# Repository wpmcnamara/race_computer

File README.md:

# Open Road Race Timing Computer

## Version 1.0

A repository with the code for the Open Road Race Timing Computer created by Patrick McNamara.

Includes the computer's software, as well as hardware description files for both the case and PCB.

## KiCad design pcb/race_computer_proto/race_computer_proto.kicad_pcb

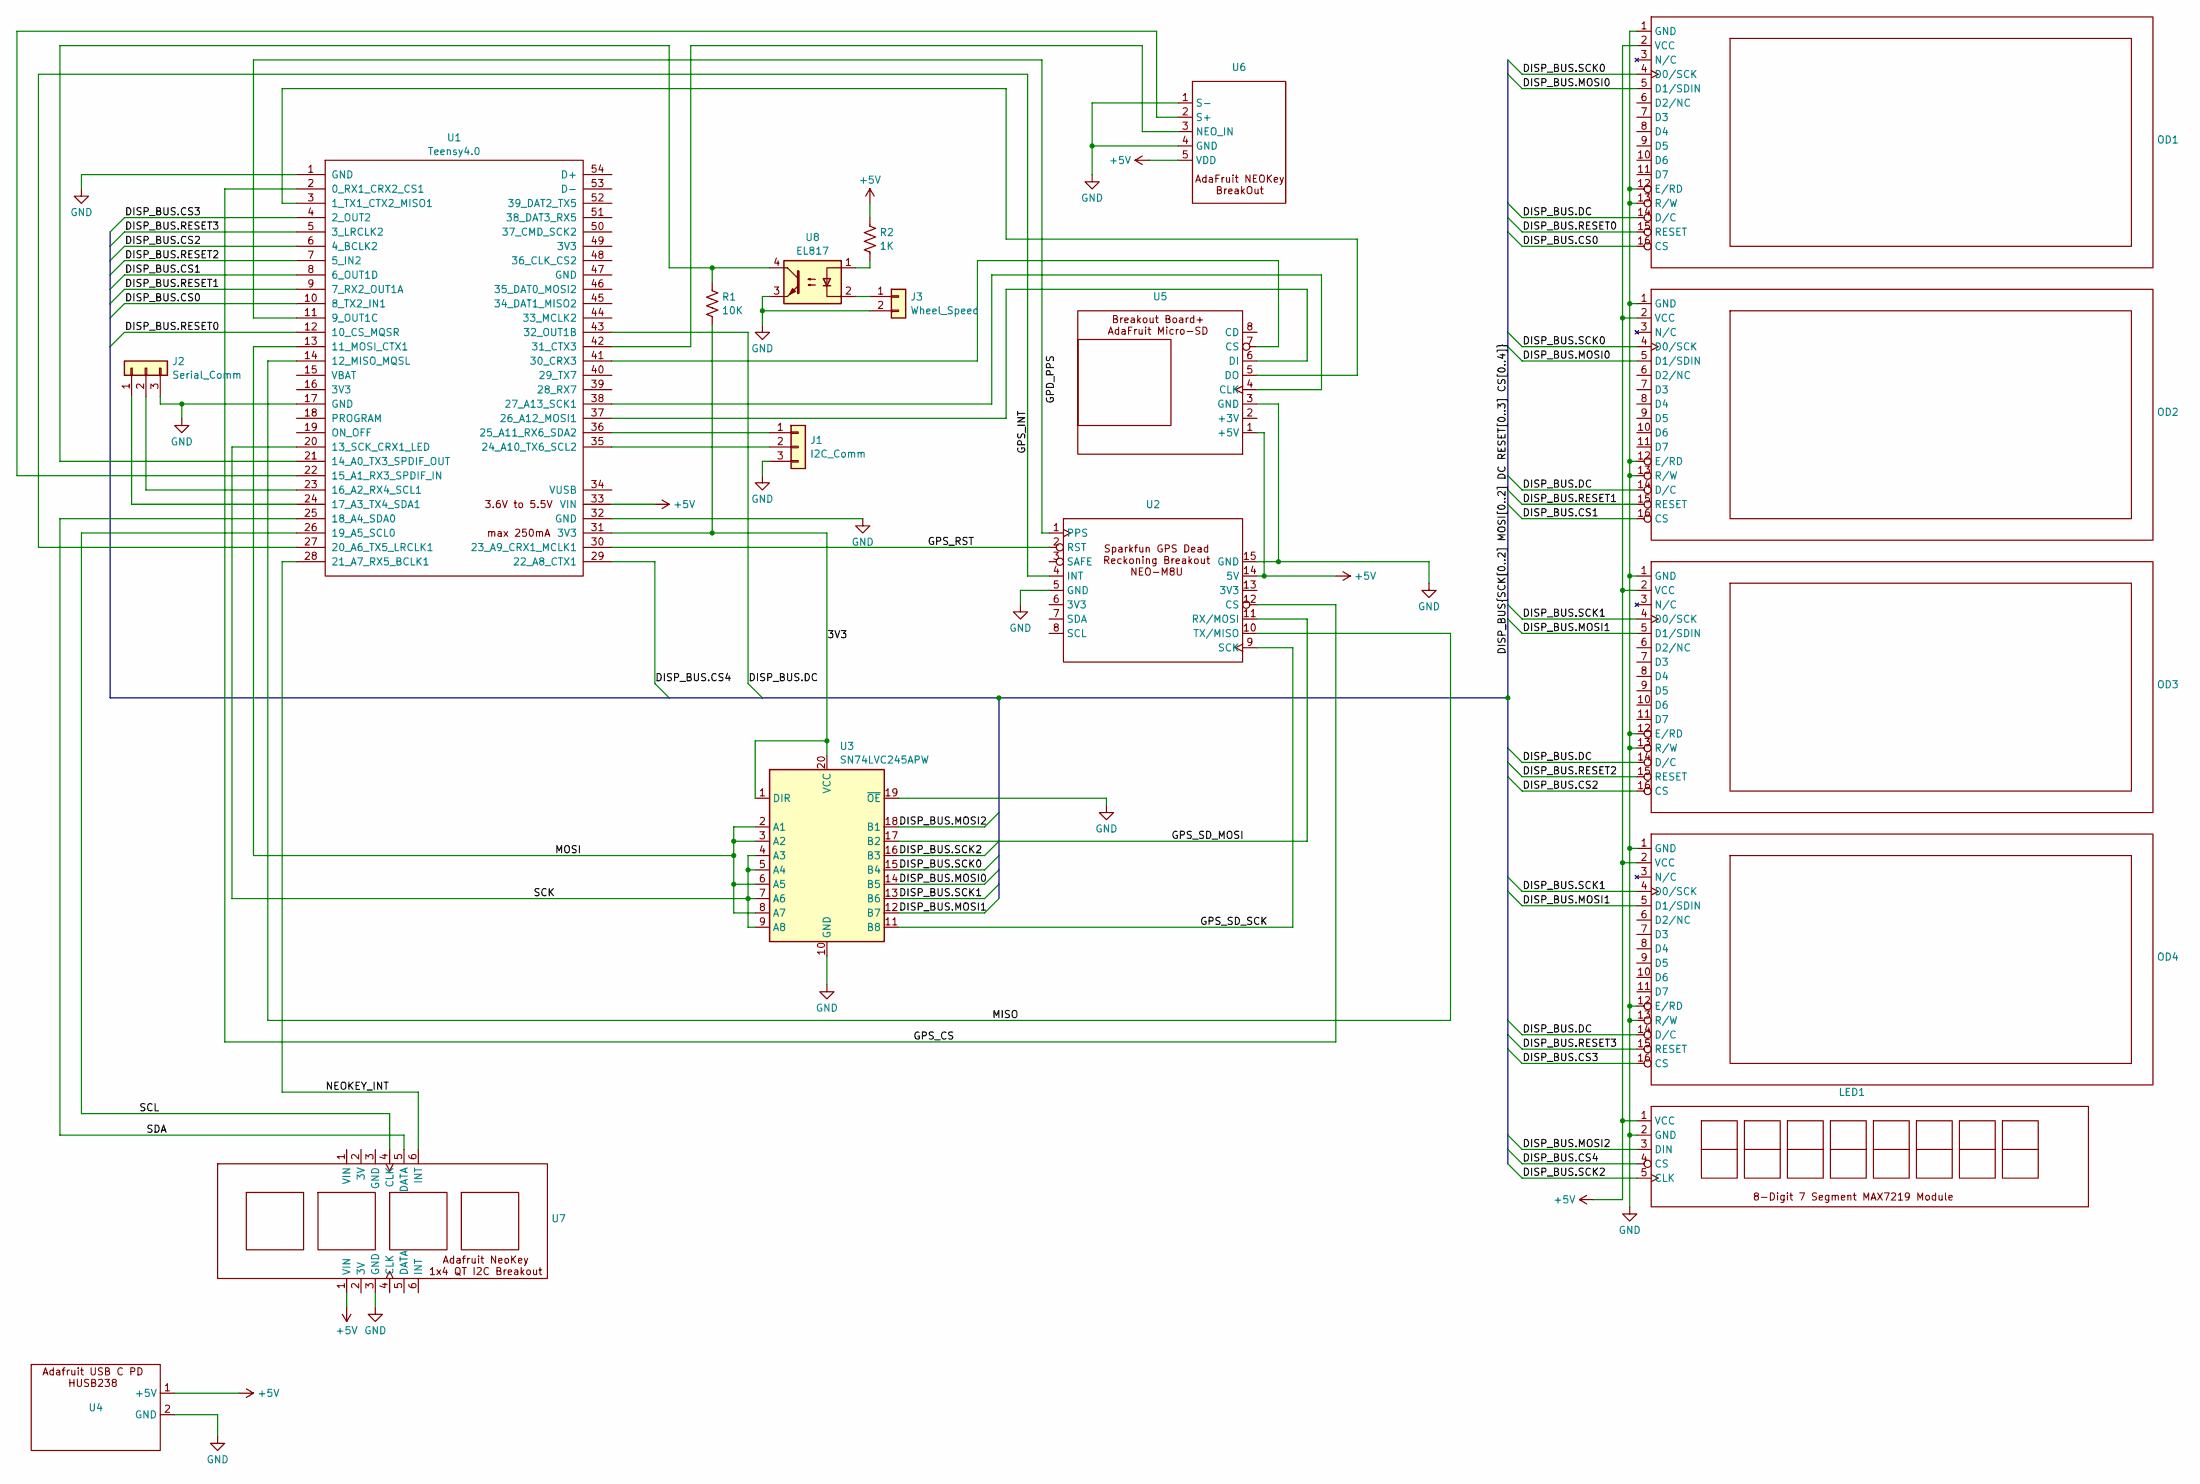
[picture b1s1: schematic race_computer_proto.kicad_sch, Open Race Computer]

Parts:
J1: I2C_Comm; JST_XH_B3B-XH-A_1x03_P2.50mm_Vertical
J2: Serial_Comm; JST_XH_B3B-XH-A_1x03_P2.50mm_Vertical
J3: Wheel_Speed; JST_XH_B2B-XH-A_1x02_P2.50mm_Vertical
LED1: 7seg_max7219_module_header
OD1, OD2, OD3, OD4: OLED_header
R1: 10K; R_Axial_DIN0204_L3.6mm_D1.6mm_P5.08mm_Horizontal
R2: 1K; R_Axial_DIN0204_L3.6mm_D1.6mm_P5.08mm_Horizontal
U1: Teensy4.0; Teensy40_reduced1
U2: SparkFun_NEO-M8U
U3: SN74LVC245APW; DIP-20_W7.62mm_Socket_LongPads
U4: power_header
U5: JST_XH_B8B-XH-A_1x08_P2.50mm_Vertical
U6: JST_XH_B5B-XH-AM_1x05_P2.50mm_Vertical
U7: JST_XH_B6B-XH-A_1x06_P2.50mm_Vertical
U8: EL817; DIP-4_W7.62mm

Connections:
+5V: LED1.1 (VCC), OD1.2 (VCC), OD2.2 (VCC), OD3.2 (VCC), OD4.2 (VCC), R2.1, U1.33 (VIN), U2.14 (5V), U4.1 (+5V), U5.1 (+5V), U6.5 (VDD), U7.1 (VIN)
/3V3: R1.2, U1.31 (3V3), U3.1 (DIR), U3.20 (VCC)
/DISP_BUS.CS0: OD1.16 (CS), U1.10 (8_TX2_IN1)
/DISP_BUS.CS1: OD2.16 (CS), U1.8 (6_OUT1D)
/DISP_BUS.CS2: OD3.16 (CS), U1.6 (4_BCLK2)
/DISP_BUS.CS3: OD4.16 (CS), U1.4 (2_OUT2)
/DISP_BUS.CS4: LED1.4 (CS), U1.29 (22_A8_CTX1)
/DISP_BUS.DC: OD1.14 (D/C), OD2.14 (D/C), OD3.14 (D/C), OD4.14 (D/C), U1.43 (32_OUT1B)
/DISP_BUS.MOSI0: OD1.5 (D1/SDIN), OD2.5 (D1/SDIN), U3.14 (B5)
/DISP_BUS.MOSI1: OD3.5 (D1/SDIN), OD4.5 (D1/SDIN), U3.12 (B7)
/DISP_BUS.MOSI2: LED1.3 (DIN), U3.18 (B1)
/DISP_BUS.RESET0: OD1.15 (RESET), U1.12 (10_CS_MQSR)
/DISP_BUS.RESET1: OD2.15 (RESET), U1.9 (7_RX2_OUT1A)
/DISP_BUS.RESET2: OD3.15 (RESET), U1.7 (5_IN2)
/DISP_BUS.RESET3: OD4.15 (RESET), U1.5 (3_LRCLK2)
/DISP_BUS.SCK0: OD1.4 (D0/SCK), OD2.4 (D0/SCK), U3.15 (B4)
/DISP_BUS.SCK1: OD3.4 (D0/SCK), OD4.4 (D0/SCK), U3.13 (B6)
/DISP_BUS.SCK2: LED1.5 (CLK), U3.16 (B3)
/GPS_CS: U1.2 (0_RX1_CRX2_CS1), U2.12 (CS)
/GPS_INT: U1.27 (20_A6_TX5_LRCLK1), U2.4 (INT)
/GPS_RST: U1.30 (23_A9_CRX1_MCLK1), U2.2 (RST)
/GPS_SD_MOSI: U2.11 (RX/MOSI), U3.17 (B2)
/GPS_SD_SCK: U2.9 (SCK), U3.11 (B8)
/MISO: U1.14 (12_MISO_MQSL), U2.10 (TX/MISO)
/MOSI: U1.13 (11_MOSI_CTX1), U3.2 (A1), U3.3 (A2), U3.6 (A5), U3.8 (A7)
/NEOKEY_INT: U1.28 (21_A7_RX5_BCLK1), U7.6 (INT)
/SCK: U1.20 (13_SCK_CRX1_LED), U3.4 (A3), U3.5 (A4), U3.7 (A6), U3.9 (A8)
/SCL: U1.26 (19_A5_SCL0), U7.4 (CLK)
/SDA: U1.25 (18_A4_SDA0), U7.5 (DATA)
GND: J1.3, J2.3, J3.2, LED1.2 (GND), OD1.1 (GND), OD1.12 (E/RD), OD1.13 (R/W), OD2.1 (GND), OD2.12 (E/RD), OD2.13 (R/W), OD3.1 (GND), OD3.12 (E/RD), OD3.13 (R/W), OD4.1 (GND), OD4.12 (E/RD), OD4.13 (R/W), U1.1 (GND), U1.17 (GND), U1.32 (GND), U2.5 (GND), U2.15 (GND), U3.10 (GND), U3.19 (~OE), U4.2 (GND), U5.3 (GND), U6.1 (S-), U6.4 (GND), U7.3 (GND), U8.3
unnamed: J1.1, U1.36 (25_A11_RX6_SDA2)
unnamed: J1.2, U1.35 (24_A10_TX6_SCL2)
unnamed: J2.1, U1.24 (17_A3_TX4_SDA1)
unnamed: J2.2, U1.23 (16_A2_RX4_SCL1)
unnamed: J3.1, U8.2
unnamed: R2.2, U8.1
unnamed: U1.3 (1_TX1_CTX2_MISO1), U5.5 (DO)
unnamed: U1.11 (9_OUT1C), U2.1 (PPS)
unnamed: R1.1, U1.21 (14_A0_TX3_SPDIF_OUT), U8.4
unnamed: U1.22 (15_A1_RX3_SPDIF_IN), U6.2 (S+)
unnamed: U1.37 (26_A12_MOSI1), U5.6 (DI)
unnamed: U1.38 (27_A13_SCK1), U5.4 (CLK)
unnamed: U1.41 (30_CRX3), U5.7 (CS)
unnamed: U1.42 (31_CTX3), U6.3 (NEO_IN)

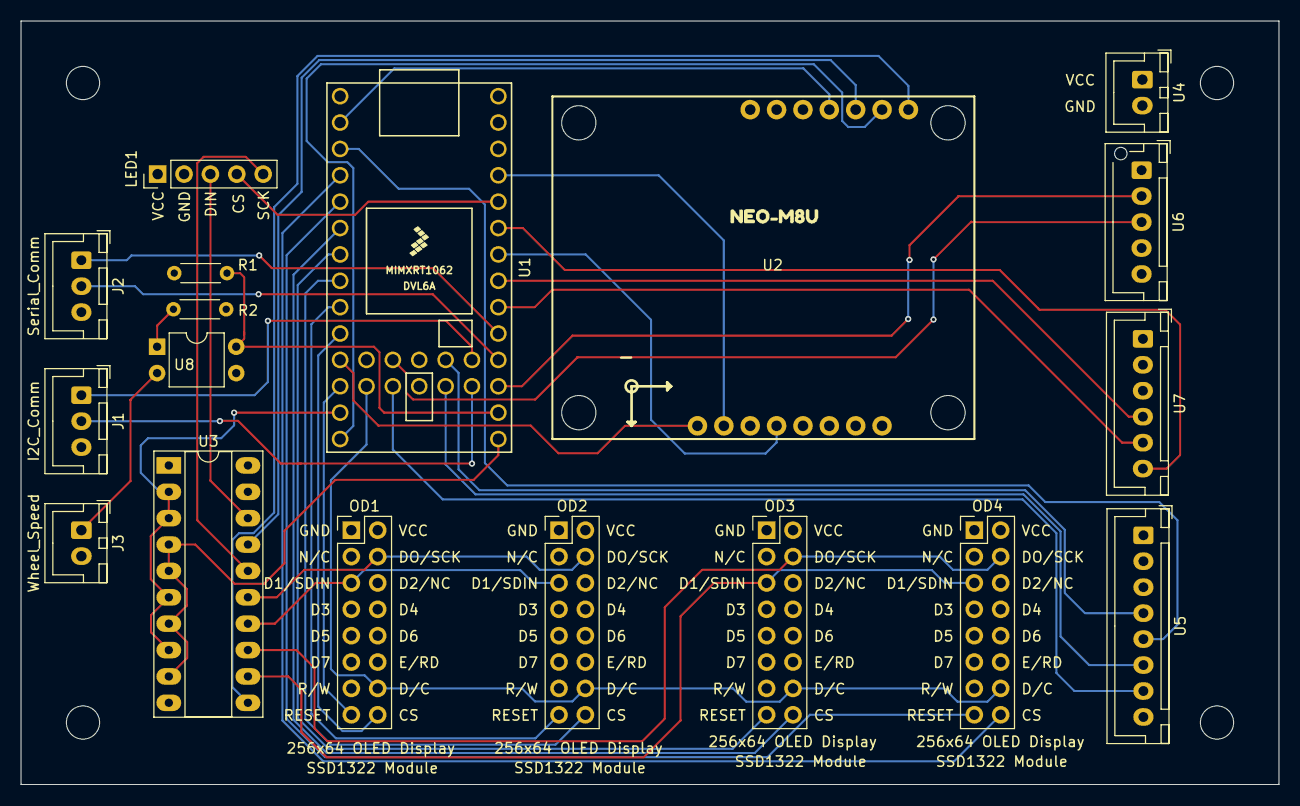
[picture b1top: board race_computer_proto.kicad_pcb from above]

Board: 4 copper layers, 121.2 x 73.5 mm, 18 parts (0 on the bottom side), 44 nets.

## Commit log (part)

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2025-08-26 Add OLED rotation for prototype board (with incorrect headers) All functions now initialize.
2025-09-07 Add missing chip select for LED display. Reorder OLED control pins so that GPS PPS signal is on Teensy pin 9. PPS must be on a pin that can be used as a timer input. Re-route PCB with above changes.
    TODO: Correct power board pinout (reversed). Correct OLED connector pinour (mirrored).
    Switch to callbacks for most GPS packet updates.
    Displays now show: time delta, speed delta, distance remaining, distance traveled, speed, and average speed.
    Enabled odometer and switched average speed calc to be based on the odometer.
2025-09-16 Convert timer callback list to an object based event list to allow more flexible use. Add bitmaps for boot splash. Completed prototype case model. Corrected neokey breakout connections on schematic a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
2025-09-20 Massive update: compiles and runs. Not road tested.
    In longer road tests, found that at stop lights, the average speed was only updating once per second. It
    turns out that it was calculating values assuming the timer "tick" was in milliseconds, when it was in
    seconds. The running timer count is the residual milliseconds. However, it was still producing "valid"
    output because it was assuming the GPS reported speed was in meters/sec, but it is actually in
    millimeters/sec. The mistaken factor of 1000 was canceling out. This has been corrected.
    This update massively reorganizes the data tracking. Structures have been brought in for the active
2025-09-20 Correct an error on the case tongue and groove. Add a set of standoffs at the vertical midpoint of the case. Add matching holes in PCB for new standoffs. Fix formatting on OLED displays.
2025-09-25 Begin restructure the display routines to make the movable between displays and on a given display, where applicable. No new display routines added, this just moved the existing ones into functions, 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
    Unfortunately the autoformatter got turned loose on gpc.cpp and I don't care to go undo it, so there are a lot of
    whitespace changes.
    Added functionality to blink the start button when starting a race leg with a delayed (synced to a start mark)
    start.
    Fixed bugs in the delayed start functionality. There was some math that wasn't quite right and, more importantly,
    the event timer apparently runs slow. To get the display to start updati
2025-09-28 Basic flesh out of the state machine code. The start/stop button lighting is fully controlled by the state machine now. The button lighting is controlled by the state machine, except for the light wh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
    Basic state machine flow is in place. Next step will be to start building out the displays for each of the states and adding
    state transition logic for some of the states that currently just pass through.
    The state machine has three main blocks:
    * au
2025-10-01 Basic handling of cycling through race legs and ending the race is in place.
    Need to leg summary and race summary displays in place.
2025-10-02 Started laying out leg and race summary and detail screens.
    I think I fixed a bug where sometimes the first push of the start/stop button wouldn't
    register. Quite a problem if you are trying to start a race and it doesn't register. I
    believe it was a race between reading the signal and the interrupt triggering. Seperated
    out flags for keypad press and start/stop press.
    Just tested and and the start/stop bug is still there... <grrr>
    Race average speed on the second leg of a race is completely wrong. Some race values
2025-10-03 Fixed bug where odometer offset at the start of a leg was being stored to the top level race instead of the active leg. This would have resulted in very erroneous timing in situations where the compu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
    Disabled the auto-end when the leg distance matched distance driven. This will rarely be the case.
    Will probably make it a config option later.
    Timestamp calculations in updateRace() were completely misbehaving. The seconds field was getting
    overwritten somehow -- I think this may be a compiler bug. Switched to converting timestampts to
    fixed point interger representations, which works well. Will probably do that anywhere timestamp
    m
2025-10-04 Corrected a bug the meant the displayed race leg and selected race leg were out of sync so the race would not end when the leg completed after a checkpoint load.
    Confirmed that the GPS data update jerkiness is not due to the event timer getting hung
    up. Race time on the LED display progresses smoothly -- it is not dependent on GPS data.
    It also doesn't us the MISO signal. So, its not a problem writing on the SPI bus. Still
    could be a read problem. May move the SD card to SPI2, though that will take some serious
    bodge work.
2025-10-06 Converted the delta time printouts to use a separate sign character rather than relying on the printf sign representation because -1/1000=0, not -0. Fixed an overflow bug due to using unsigned long r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
2025-10-07 Switched to an SPI lock flag rather than enabling/disabling events. A bit cleaner and it lets me flag SPI collisions while doing development and testing. Should probably be switched over to a mutex f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
2025-10-11 Convert the waypoint display to scale precision on mileage and to change units between hours, minutes, and seconds on time to point.
    Change the GPS instantaneous speed to be the a running average of the last five samples to
    smooth out the fluctuations due to SA. At five samples, its still only about 250ms lagging
    real time.
2025-10-13 Rev version and turn off some debug noise. Add drive definitions for BBORR.
2025-10-15 Waypoint updates
2025-12-02 Correct the algo used to calculate the time delta. It now looks at how long it should have taken to travel the distance covered versus how long it actually took.
2025-12-20 Add rev info to schematic sheet. Remove gerbers and other unneeded files from repo.
2026-01-04 Case for v2 of the proto dev board and computer. Note this design was done with mainline FreeCAD rather than the Link Branch.
2026-01-06 Update pin definitions in the BSP header to match new PCB layout. Fix a compile Bug. Add datasheet.
2026-01-31 Updated case for the new PCB. Includes models for electronics. Minor PCB fix -- GND connection was missing from the NeoKey connector, so the button would not register when pushed.
2026-02-20 Begin revamp of the menuing system. This plumbs in the new menu tree. Menu navigation works, but no functions are tied in yet.
2026-02-24 Firmware update functions now show progress bar and status message. keypad color handling improved. Keys are white when pressed, and return to the currently set color when released. Ability to set in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
2026-02-28 Both OLED and LED brightness functions work and are plumbed into the menu system. Ajdusted satelite and lock icon size and adjusted lock type and satellite count appropriately. Added states for scree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
2026-03-10 * Added screen blanking functionality and timeout configuration. * Added menus for system info and reboot. * System information menu is not yet active. Needs PCB version stored in EEPROM, among other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
2026-03-14 This is a big change and probably should have been broken up into multiple commits. Such is the development life.
    Leg adjustment functionality is in, though not quite complete. Still need to update speed when changing distance. Further,
    Updating distance currently changes the time, but should probably change the target speed. Changing the speed does change the
    time, and I think that is correct. Also need to add a menu entry that restores the current leg settings to those that were
    calculated by the computer -- completely remove any edits made after that.
    The other big change is the switch from JSON to YAML for config files and race definitions. Along with that, Race Point
    files are no
2026-03-15 Changing time adjusts target speed -- fixed problem where incrementing/decrementing the hours field also incremented/decremented the 10s hours field. Changing distance adjusts target speed. Changing 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
2026-03-18 Add hardware version info in EEPROM. Still need to add the initial value configuration for first boot. Add functionality to the "System Information" menu to display the hardware info. Turn back on th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
2026-03-25 Drive distance completed wasn't being updated, for the overall race, at the end of a leg.
2026-04-03 Convert drive_distance, speed_range to driveDistance, speedRange in race definitions and race loader. This makes the code incompatible with earlier race files. Split setting of race and leg data stru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
2026-04-11 Change the way we handle internal timer ticks and retrieving timestamps. The PPS timer now only increments the seconds count. Timestamp retrieval gets the actual millisecond count from the timer insi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
    All internal data values are now stored as floating point 64bit doubles. The Teensy4 has native 64bit float support, so math performance is fine (beyond
    being a 600Mhz+ processor). Almost all conversions to
2026-04-11 Added option to reset all configuration settings -- currently just removes the settings save file and reboots Added option to toggle automatic adjustment of leg times based on race time delta
    Corrected displays leg target speed in the leg summary.
    Corrected target time in the race summary display.
    Correct calculation of race time delta in GPS callback -- use current expected race average rather than finishing average.
    Correct leg speed delta calculation in end of leg race update.
2026-04-12 Add a targetTime value to race/leg data. Add a targetTime complete value to race/leg data.
    Add configuration for where the speed delta for speed band comparisons comes from. We also allow it
    to be disabled, in which case the keypad LEDs won't be lit during a race.
2026-04-12 Add all race values updated in updateRace() to the race checkpoint so that we restore all state if we load a checkpoint. Adjust order of initialization so that race level data is restored before the 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
2026-04-13 Switch the adjuste leg target time back the time delta adjusted leg time.
2026-04-18 Clean up some Serial logging output
    Stop collecting GPS updates as soon as the timer is stopped when the start/stop button is pressed to stop a leg. This will ensure that
    GPS odometer updates don't keep getting added until the time mark frame comes in.
    When we update the leg and race at the end of a leg, we need to update all values that depend on race time since the race time will get
    updated by the time mark for from the GPS and we should calculate everything based on that time, not the prior GPS frame, which could be
    off by as much as 10ms.
    log adjustedAverageSpeed and adjustedSpeedDelta
2026-04-18 Massive update of the race data structure. Code has been updated to the point of compiling, but not run or debugged. Hopefully this simplifies some of data debugging that has been problematic.
2026-04-19 Fix logging header Identified and fixed the cause of timestamps occasionally jumping back by one second.
2026-04-19 Missing comma in logging header. Add formatting to log values to clean up floating point mess.
2026-04-20 Add race and practice definitions through Grand Sport (155mph)
2026-04-20 Add the 100 and 105 class for touring
2026-04-21 Fix 155 name
2026-05-11 Correct race definition file.

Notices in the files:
pcb/race_computer_proto/race_computer_proto.kicad_pcb:
©2025 Patrick McNamara
